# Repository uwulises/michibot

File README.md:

# michibot

Michi (cat) intentionally designed for work with a Raspberry Pi Pico + micropython. 

## Ref
- Robot Cat Nybble <https://www.petoi.com/pages/nybble-cutest-bionic-robot-cat>
- OpenCat <https://www.thingiverse.com/thing:4015171/files>

Ideas & examples may be found here <https://github.com/raspberrypi/pico-examples>

# Materials
- Raspberry Pi Pico
- Servo MG90
- Raspberry Pi Zero 2W

# Brainstorming/layout/PCBdesign

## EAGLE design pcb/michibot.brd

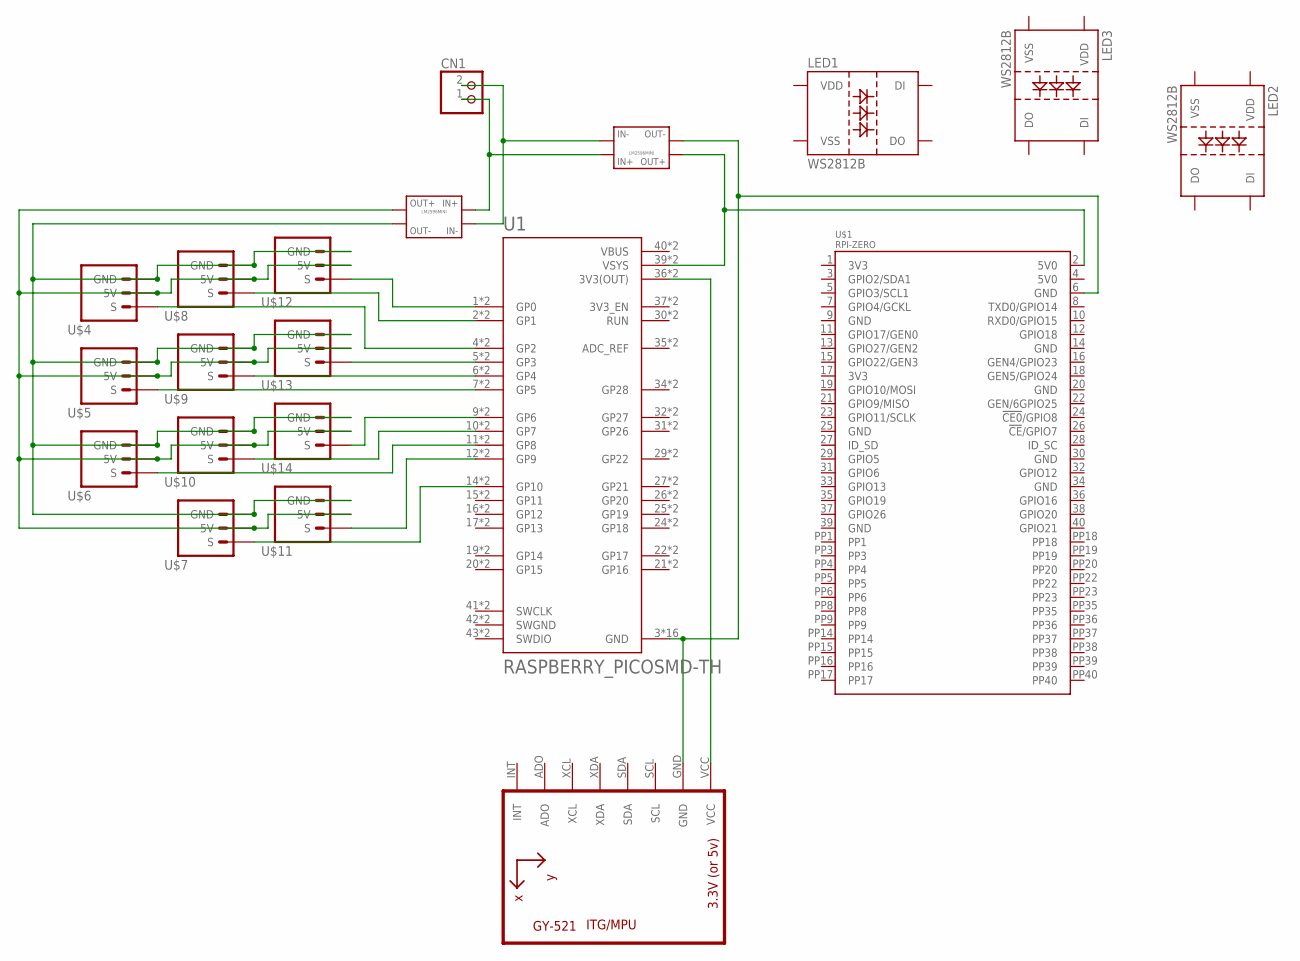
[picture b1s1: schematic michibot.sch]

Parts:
CN1: JST_2PIN-THM; JST-PH-2-THM
LED1, LED2, LED3: WS2812B
U1: RASPBERRY_PICOSMD-TH; PICO-PKG
U2: GY-521MPU6050; GY-521
U$1: RPI-ZERO; RASP_PI_ZERO_BOARD_FULL
U$2, U$3: BB-LM2596MINI
U$4, U$5, U$6, U$7, U$8, U$9, U$10, U$11, U$12, U$13, U$14: BB-PIN3

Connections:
5V0@1: U1.39 (VSYS), U1.P$39 (VSYS), U$1.2 (5V0), U$2.OUT+
GND@8: U1.3 (GND), U1.8 (GND), U1.13 (GND), U1.18 (GND), U1.23 (GND), U1.28 (GND), U1.33 (GND), U1.38 (GND), U1.P$3 (GND), U1.P$8 (GND), U1.P$13 (GND), U1.P$18 (GND), U1.P$23 (GND), U1.P$28 (GND), U1.P$33 (GND), U1.P$38 (GND), U2.GND, U$1.6 (GND), U$2.OUT-
unnamed: U1.36 (3V3(OUT)), U1.P$36 (3V3(OUT)), U2.VCC
unnamed: U$3.OUT+, U$4.2 (5V), U$5.2 (5V), U$6.2 (5V), U$7.2 (5V), U$8.2 (5V), U$9.2 (5V), U$10.2 (5V), U$11.2 (5V), U$12.2 (5V), U$13.2 (5V), U$14.2 (5V)
unnamed: U$3.OUT-, U$4.1 (GND), U$5.1 (GND), U$6.1 (GND), U$7.1 (GND), U$8.1 (GND), U$9.1 (GND), U$10.1 (GND), U$11.1 (GND), U$12.1 (GND), U$13.1 (GND), U$14.1 (GND)
unnamed: CN1.1 (2), U$2.IN+, U$3.IN+
unnamed: CN1.2 (1), U$2.IN-, U$3.IN-
unnamed: U1.5 (GP3), U1.P$5 (GP3), U$13.3 (S)
unnamed: U1.1 (GP0), U1.P$1 (GP0), U$12.3 (S)
unnamed: U1.2 (GP1), U1.P$2 (GP1), U$8.3 (S)
unnamed: U1.4 (GP2), U1.P$4 (GP2), U$4.3 (S)
unnamed: U1.6 (GP4), U1.P$6 (GP4), U$9.3 (S)
unnamed: U1.7 (GP5), U1.P$7 (GP5), U$5.3 (S)
unnamed: U1.9 (GP6), U1.P$9 (GP6), U$14.3 (S)
unnamed: U1.10 (GP7), U1.P$10 (GP7), U$10.3 (S)
unnamed: U1.11 (GP8), U1.P$11 (GP8), U$6.3 (S)
unnamed: U1.12 (GP9), U1.P$12 (GP9), U$11.3 (S)
unnamed: U1.14 (GP10), U1.P$14 (GP10), U$7.3 (S)
SWGND: U1.42 (SWGND), U1.P$42 (SWGND)
VBUS: U1.40 (VBUS), U1.P$40 (VBUS)

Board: 2 copper layers, 20 parts (0 on the bottom side), 20 nets, no tracks yet.

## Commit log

2022-08-08 add coarse motion
2023-02-04 Brainstorm 04/02
    Raspberry Pi Pico
    Raspberry Pi Zero 2W
2023-02-06 started michibot's pcb
2023-02-09 simple servo class
2023-02-09 testing every servo with classic sweep move
2023-02-09 update servo class
2023-02-17 add coarse inverse kinematics for left leg
2023-02-17 edit inverse kinematics
2023-02-17 update ik
2023-02-17 rename layout image
2023-04-12 idk, but just in case:)
